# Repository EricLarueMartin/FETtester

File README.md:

# FETtester
Board to attach to an Arduino to characterize transistors.

Allows adjusting drain (collector) and gate (base) voltage and reading:
gate-source (base-emitter) voltage, 
drain-source (collector-emitter) voltage,
gate (base) current,
drain (collector) current,
and temperature.

Values are level shifted by op amp circuits and measured on the Arduino ADCs.

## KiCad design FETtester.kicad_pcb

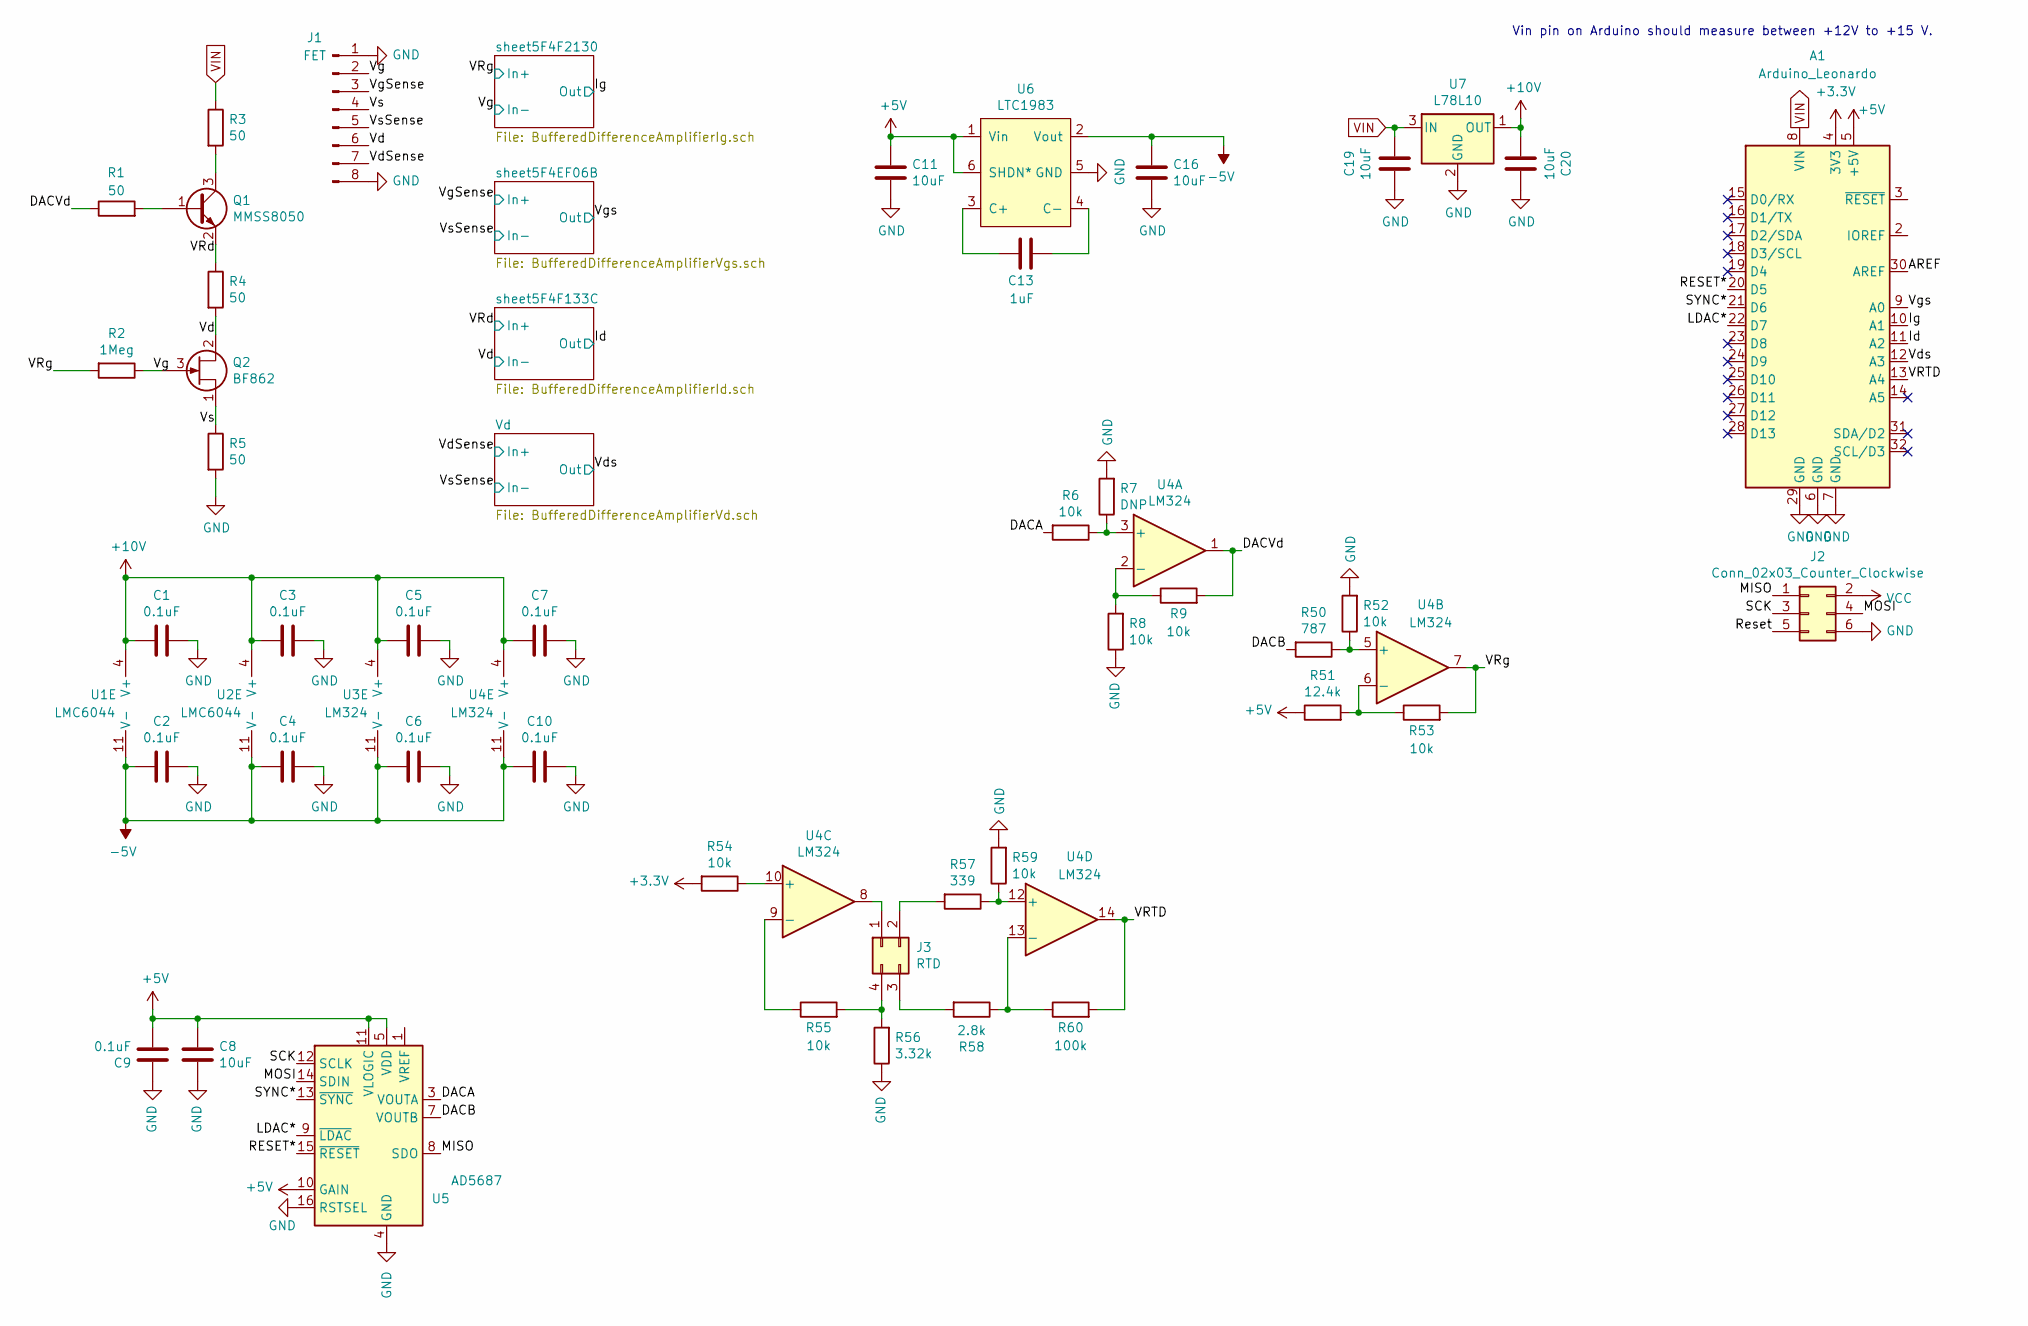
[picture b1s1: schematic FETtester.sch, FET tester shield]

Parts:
A1: Arduino_Leonardo; Arduino_UNO_R3_WithMountingHoles
C1, C2, C3, C4, C5, C6, C7, C9, C10: 0.1uF; C_0603_1608Metric
C8, C11, C16, C19, C20: 10uF; C_0603_1608Metric
C13: 1uF; C_0603_1608Metric
J1: FET; PinHeader_1x08_P2.54mm_Vertical
J2: Conn_02x03_Counter_Clockwise; PinSocket_2x03_P2.54mm_Vertical
J3: RTD; DIN_4
Q1: MMSS8050; SOT-23
Q2: BF862; SOT-23
R1, R3, R4, R5: 50; R_0603_1608Metric
R2: 1Meg; R_0603_1608Metric
R6, R8, R9, R52, R53, R54, R55, R59: 10k; R_0603_1608Metric
R7: DNP; R_0603_1608Metric
R50: 787; R_0603_1608Metric
R51: 12.4k; R_0603_1608Metric
R56: 3.32k; R_0603_1608Metric
R57: 339; R_0603_1608Metric
R58: 2.8k; R_0603_1608Metric
R60: 100k; R_0603_1608Metric
U1, U2: LMC6044; SOIC-14_3.9x8.7mm_P1.27mm
U3, U4: LM324; SOIC-14_3.9x8.7mm_P1.27mm
U5: AD5687; TSSOP-16_4.4x5mm_P0.65mm
U6: LTC1983; TSOT-23-6
U7: L78L10; SOT-89-3

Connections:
+3V3: A1.4 (3V3), R54.2
+5V: A1.5 (+5V), C8.1, C9.2, C11.1, R51.1, U5.5 (VDD), U5.10 (GAIN), U5.11 (VLOGIC), U6.1 (Vin), U6.6 (SHDN*); also elsewhere on the board
+10V: C1.2, C3.2, C5.2, C7.2, C20.2, U1.4 (V+), U2.4 (V+), U3.4 (V+), U4.4 (V+), U7.1 (OUT)
-5V: C2.2, C4.2, C6.2, C10.2, C16.1, U1.11 (V-), U2.11 (V-), U3.11 (V-), U4.11 (V-), U6.2 (Vout)
/AREF: A1.30 (AREF)
/DACA: R6.2, U5.3 (VOUTA)
/DACB: R50.2, U5.7 (VOUTB)
/DACVd: R1.1, R9.2, U4.1
/Id: A1.11 (A2); also elsewhere on the board
/Ig: A1.10 (A1); also elsewhere on the board
/LDAC*: A1.22 (D7), U5.9 (~LDAC)
/MISO: J2.1, U5.8 (SDO)
/MOSI: J2.4, U5.14 (SDIN)
/RESET*: A1.20 (D5), U5.15 (~RESET)
/Reset: J2.5
/SCK: J2.3, U5.12 (SCLK)
/SYNC*: A1.21 (D6), U5.13 (~SYNC)
/VRTD: A1.13 (A4), R60.2, U4.14
/VRd: Q1.2 (E), R4.1; also elsewhere on the board
/VRg: R2.2, R53.2, U4.7; also elsewhere on the board
/Vd: J1.6, Q2.2 (D), R4.2; also elsewhere on the board
/VdSense: J1.7; also elsewhere on the board
/Vds: A1.12 (A3); also elsewhere on the board
/Vg: J1.2, Q2.3 (G), R2.1; also elsewhere on the board
/VgSense: J1.3; also elsewhere on the board
/Vgs: A1.9 (A0); also elsewhere on the board
/Vs: J1.4, Q2.1 (S), R5.1
/VsSense: J1.5; also elsewhere on the board
GND: A1.6 (GND), A1.7 (GND), A1.29 (GND), C1.1, C2.1, C3.1, C4.1, C5.1, C6.1, C7.1, C8.2, C9.1, C10.1, C11.2, C16.2, C19.2, C20.1, J1.1, J1.8, J2.6, R5.2, R7.2, R8.1, R52.2, R56.1, R59.2, U5.4 (GND), U5.16 (RSTSEL), U6.5 (GND), U7.2 (GND); also elsewhere on the board
unnamed: C13.1, U6.3 (C+)
unnamed: C13.2, U6.4 (C-)
unnamed: J3.1, U4.8
unnamed: J3.2, R57.2
unnamed: J3.3, R58.2
unnamed: J3.4, R55.2, R56.2
unnamed: Q1.1 (B), R1.2
unnamed: Q1.3 (C), R3.2
unnamed: R6.1, R7.1, U4.3 (+)
unnamed: R8.2, R9.1, U4.2 (-)
unnamed: R50.1, R52.1, U4.5 (+)
unnamed: R51.2, R53.1, U4.6 (-)
unnamed: R54.1, U4.10 (+)
unnamed: R55.1, U4.9 (-)
unnamed: R57.1, R59.1, U4.12 (+)
unnamed: R58.1, R60.1, U4.13 (-)
VCC: J2.2
VIN: A1.8 (VIN), C19.1, R3.1, U7.3 (IN)

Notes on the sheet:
Vin pin on Arduino should measure between +12V to +15 V.

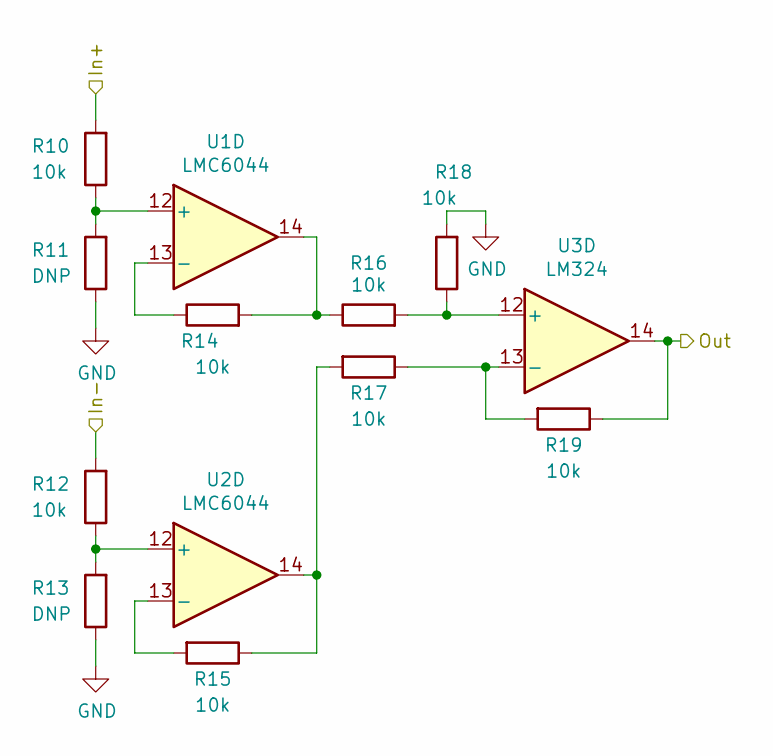
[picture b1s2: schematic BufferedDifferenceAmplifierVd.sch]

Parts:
R10, R12, R14, R15, R16, R17, R18, R19: 10k; R_0603_1608Metric
R11, R13: DNP; R_0603_1608Metric
U1, U2: LMC6044; SOIC-14_3.9x8.7mm_P1.27mm
U3: LM324; SOIC-14_3.9x8.7mm_P1.27mm

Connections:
/VdSense: R10.2; also elsewhere on the board
/Vds: R19.1, U3.14; also elsewhere on the board
/VsSense: R12.2; also elsewhere on the board
GND: R11.1, R13.1, R18.2; also elsewhere on the board
unnamed: R10.1, R11.2, U1.12 (+)
unnamed: R12.1, R13.2, U2.12 (+)
unnamed: R14.1, U1.13 (-)
unnamed: R14.2, R16.1, U1.14
unnamed: R15.1, R17.2, U2.14
unnamed: R15.2, U2.13 (-)
unnamed: R16.2, R18.1, U3.12 (+)
unnamed: R17.1, R19.2, U3.13 (-)

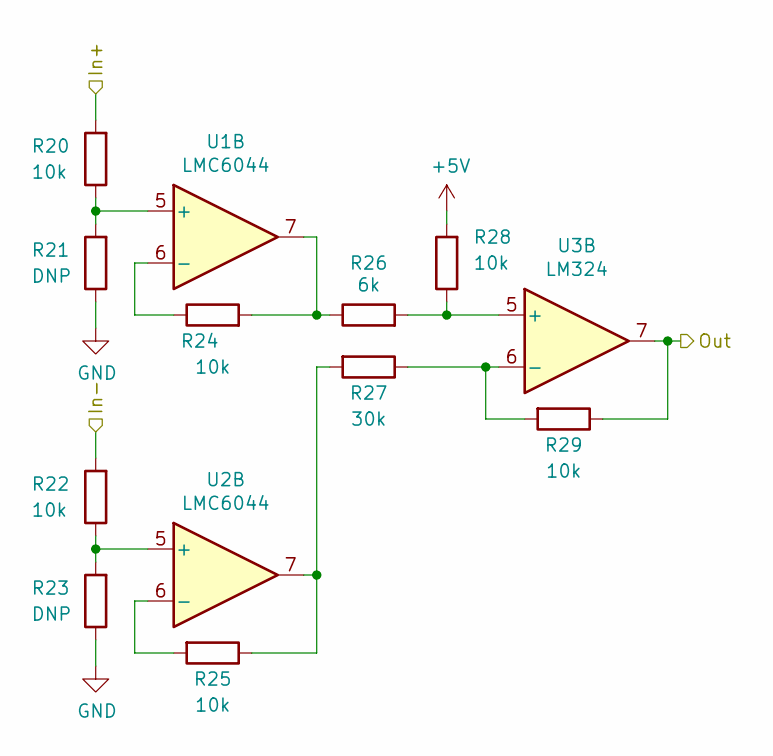
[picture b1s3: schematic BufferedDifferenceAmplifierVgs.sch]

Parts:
R20, R22, R24, R25, R28, R29: 10k; R_0603_1608Metric
R21, R23: DNP; R_0603_1608Metric
R26: 6k; R_0603_1608Metric
R27: 30k; R_0603_1608Metric
U1, U2: LMC6044; SOIC-14_3.9x8.7mm_P1.27mm
U3: LM324; SOIC-14_3.9x8.7mm_P1.27mm

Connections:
+5V: R28.2; also elsewhere on the board
/VgSense: R20.2; also elsewhere on the board
/Vgs: R29.1, U3.7; also elsewhere on the board
/VsSense: R22.2; also elsewhere on the board
GND: R21.1, R23.1; also elsewhere on the board
unnamed: R20.1, R21.2, U1.5 (+)
unnamed: R22.1, R23.2, U2.5 (+)
unnamed: R24.1, U1.6 (-)
unnamed: R24.2, R26.1, U1.7
unnamed: R25.1, R27.2, U2.7
unnamed: R25.2, U2.6 (-)
unnamed: R26.2, R28.1, U3.5 (+)
unnamed: R27.1, R29.2, U3.6 (-)

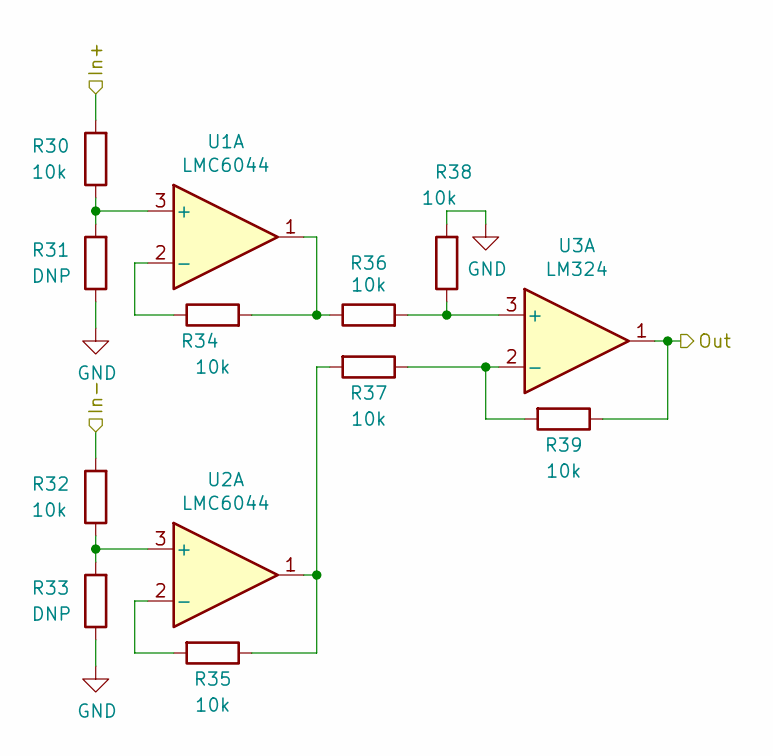
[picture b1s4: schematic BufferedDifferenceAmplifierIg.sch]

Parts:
R30, R32, R34, R35, R36, R37, R38, R39: 10k; R_0603_1608Metric
R31, R33: DNP; R_0603_1608Metric
U1, U2: LMC6044; SOIC-14_3.9x8.7mm_P1.27mm
U3: LM324; SOIC-14_3.9x8.7mm_P1.27mm

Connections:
/Ig: R39.1, U3.1; also elsewhere on the board
/VRg: R30.2; also elsewhere on the board
/Vg: R32.2; also elsewhere on the board
GND: R31.1, R33.1, R38.2; also elsewhere on the board
unnamed: R30.1, R31.2, U1.3 (+)
unnamed: R32.1, R33.2, U2.3 (+)
unnamed: R34.1, U1.2 (-)
unnamed: R34.2, R36.1, U1.1
unnamed: R35.1, R37.2, U2.1
unnamed: R35.2, U2.2 (-)
unnamed: R36.2, R38.1, U3.3 (+)
unnamed: R37.1, R39.2, U3.2 (-)

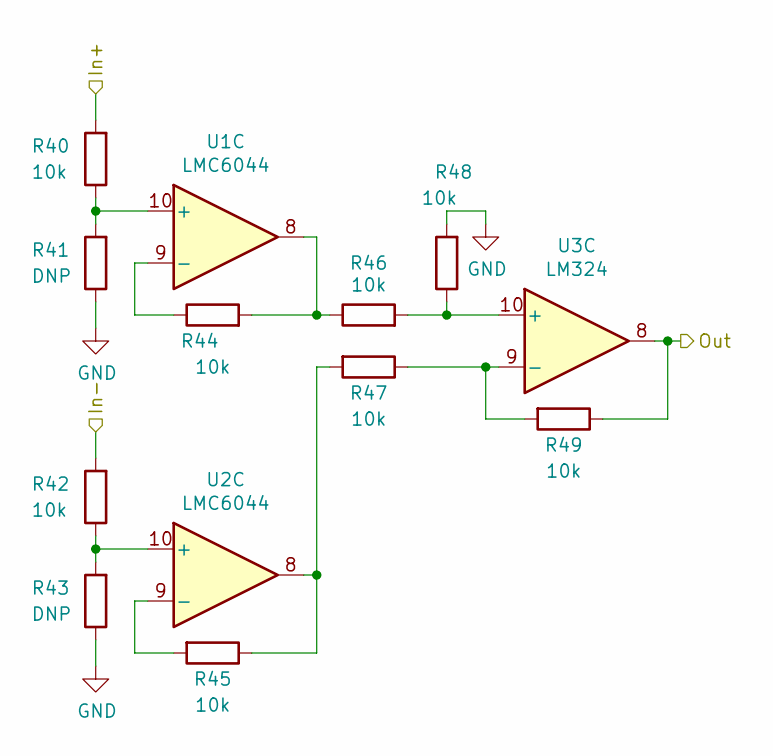
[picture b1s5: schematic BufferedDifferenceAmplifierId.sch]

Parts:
R40, R42, R44, R45, R46, R47, R48, R49: 10k; R_0603_1608Metric
R41, R43: DNP; R_0603_1608Metric
U1, U2: LMC6044; SOIC-14_3.9x8.7mm_P1.27mm
U3: LM324; SOIC-14_3.9x8.7mm_P1.27mm

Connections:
/Id: R49.1, U3.8; also elsewhere on the board
/VRd: R40.2; also elsewhere on the board
/Vd: R42.2; also elsewhere on the board
GND: R41.1, R43.1, R48.2; also elsewhere on the board
unnamed: R40.1, R41.2, U1.10 (+)
unnamed: R42.1, R43.2, U2.10 (+)
unnamed: R44.1, U1.9 (-)
unnamed: R44.2, R46.1, U1.8
unnamed: R45.1, R47.2, U2.8
unnamed: R45.2, U2.9 (-)
unnamed: R46.2, R48.1, U3.10 (+)
unnamed: R47.1, R49.2, U3.9 (-)

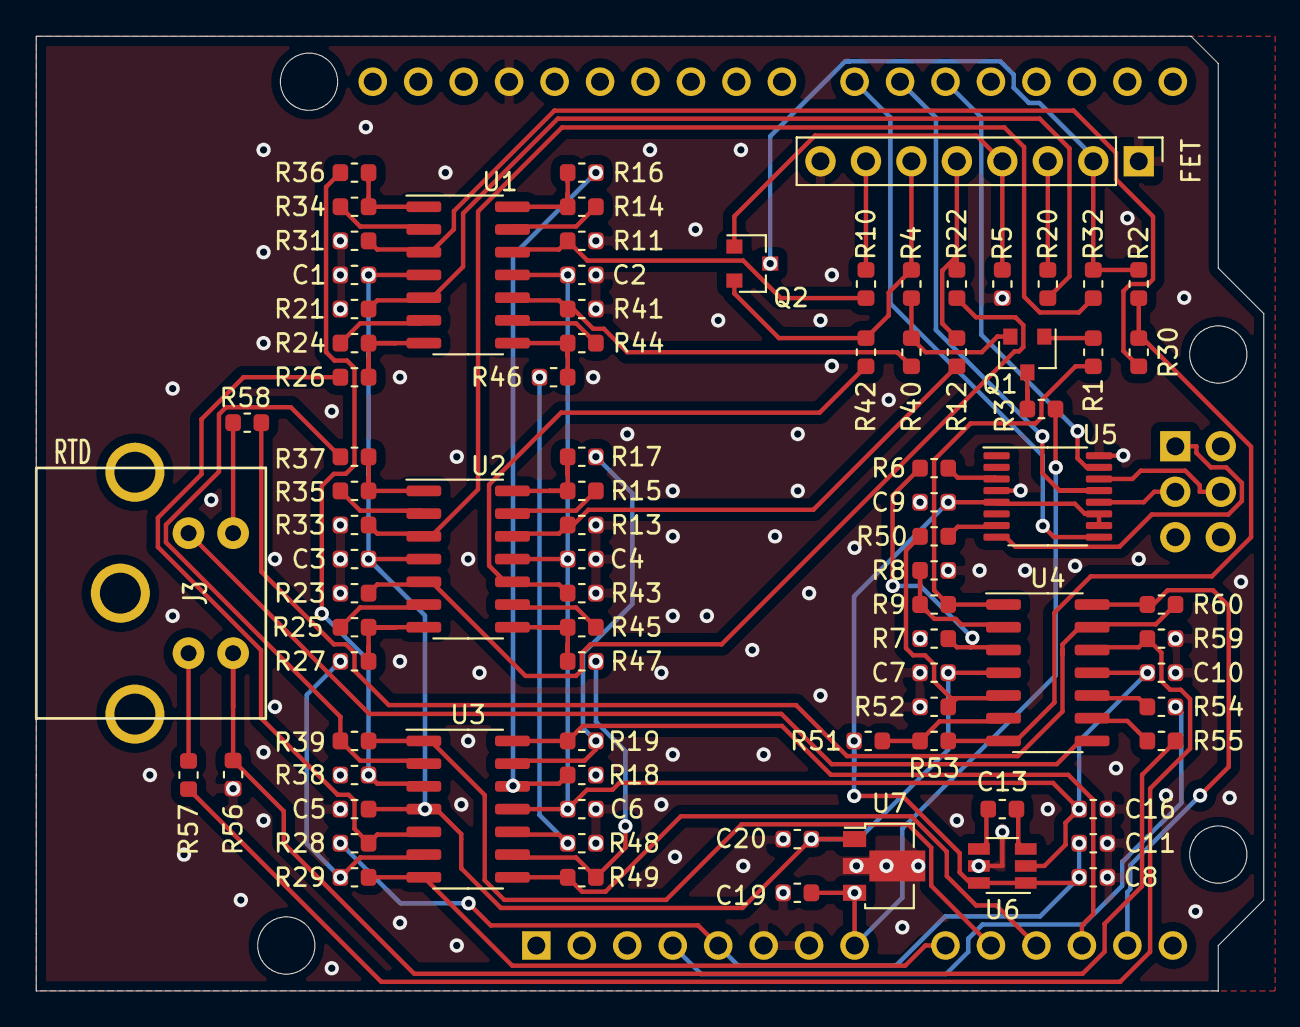
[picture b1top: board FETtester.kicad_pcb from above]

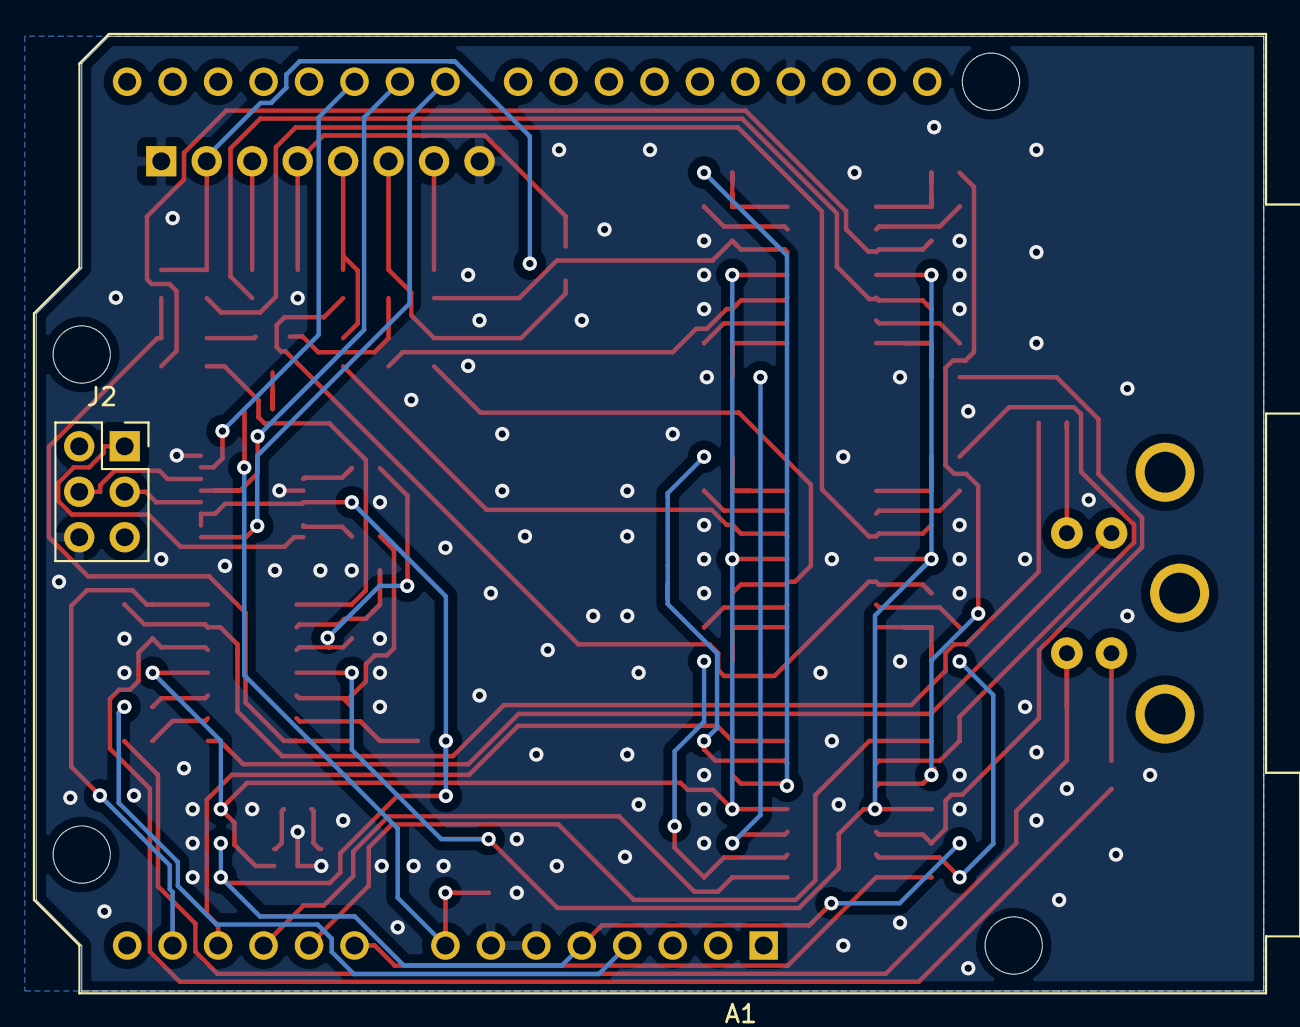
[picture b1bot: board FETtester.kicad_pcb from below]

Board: 2 copper layers, 68.6 x 53.3 mm, 88 parts (2 on the bottom side), 76 nets.

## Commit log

2020-08-11 Minor routing changes.
2020-08-17 Added negative swing on gate-source bias and RTD connection.
2020-08-31 Fixed missing connection for RTD line.
